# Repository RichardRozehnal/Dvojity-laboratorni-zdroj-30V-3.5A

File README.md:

# Dvojitý laboratorní zdroj 30V / 3.5A

Napájecí zdroj s nastavitelným výstupním napětím 0-30V a nastavitelným omezením výstupního proudu 0-3.5A. Omezení proudu je indikováno červenou LEDkou.
Jedná se o dvoukanálový laboratorní zdroj.  Maximální proud, který jsem dostal z kanálu 1 je 3.5A a z kanálu 2 3.7A (po zkratování výstupních svorek).<br>
Použitý transformátor má několik sekundárních vinutí. Z nich jsem využil dvě hlavní, každé s výstupem 25V/4A a dvě pomocná s výstupem 12V/2A pro napájení panelových měřidel a ventilátorů.<br>
Zapnutí ventilátorů jsem nastavil na teplotu tranzistorů 60C, vypíná se při 46C.<br>
Čelní panel jsem nakreslil v Inkscape, vytiskl a potom přežehlil laminovací folií pro lepší vzhled, zpevnění a také ochranu tisku.<br>
Pro regulaci výstupního napětí a omezení proudu jsou použity 5-ti otáčkové potenciometry.<br>
Rozměr zdroje je 24cm x 15cm x 25cm, větrací otvory mají průměr 7mm a rozteč 10.4mm.

## Měření tvrdosti zdroje

| **nastavené napětí / napětí po zatížení (kanál 1 / kanál 2)** | **0.45A**   | **0.89A**   | **1.82A**     | **3A**         | **3.5A**      |
| :-----------------------------------------------------------: | :---------: | :---------: | :-----------: | :------------: | :-----------: |
| 5V                                                            | 5V / 5V     | 5V / 5V     | 5V / 5V       | 5V / 5V        | 5V / 5V       |
| 10V                                                           | 10V / 10V   | 10V / 10V   | 10V / 10V     | 10V / 10V      | 10V / 10V     |
| 20V                                                           | 20V / 20V   | 20V / 20V   | 20V /20V      | 20V / 20V      | 20V / 20V     |
| 25V                                                           |             |             |               | 24.5 V / 24.2V | 23.6V / 23.6V |
| 30V                                                           | 30V / 29.8V | 29V / 28.8V | 26.8V / 26.7V |                |               |

## Měření teplot a proudů (při otevřeném šasi)

|                                                       | nastavený proud  | Kanál 1  | Kanál 2  |
| ----------------------------------------------------- | :--------------: | :------: | :------: |
| Teplota tranzistorů KD502 (bez zapnutého ventilátoru) | 1A               | 54C      | 58C      |
| Teplota tranzistorů KD502 (bez zapnutého ventilátoru) | 2A               | přes 70C | přes 80C |
| Teplota tranzistorů KD502 (se zapnutým ventilátorem)  | 2A               | 55C      | 63C      |
| Teplota tranzistorů KD502 (se zapnutým ventilátorem)  | 3A               | 65C      | 76C      |
| Teplota tranzistorů KD502 (se zapnutým ventilátorem)  | max. 3.5A / 3.7A | 67C      | 84C      |
| Teplota rezistorů R7 a R8                             | 3A               | 80C      | 81C      |
| Teplota rezistorů R7 a R8                             | max. 3.5A / 3.7A | 92C      | 107C     |

## Seznam součástek

| **Ref**                          | **Qnty** | **Value**                               | **Cmp name** |
| -------------------------------- | :------: | --------------------------------------- | ------------ |
| 230V1,                           | 1        | 230V                                    | Conn\_01x02  |
| C1, C2,                          | 2        | 4700uF/63V/105C                         | CP           |
| C3, C4,                          | 2        | 47uF/50V                                | CP           |
| C5,                              | 1        | 220n CF1                                | C            |
| C6, C9,                          | 2        | 100pF                                   | C            |
| C7,                              | 1        | 10uF/50V                                | CP           |
| C8,                              | 1        | 330pF                                   | C            |
| C10, C14,                        | 2        | 100nF                                   | C            |
| C13,                             | 1        | 330nF                                   | C            |
| C15, C16,                        | 2        | 1000uF/25V                              | CP           |
| D1, D2, D3, D4,                  | 4        | P1000M                                  | D            |
| D5, D6,                          | 2        | 1N4148                                  | D            |
| D7,                              | 1        | 1N4734A (5V6)                           | D\_Zener     |
| D8,                              | 1        | BZX83V005.6                             | D\_Zener     |
| D9, D10,                         | 2        | 1N4148                                  | D            |
| D11, D14,                        | 2        | S1M                                     | D            |
| D12,                             | 1        | LED 5mm červená                         | LED          |
| D13,                             | 1        | KBP307                                  | KBP307       |
| D15,                             | 1        | LED 5mm žlutá                           | LED          |
| F1,                              | 1        | 6A                                      | Fuse         |
| F2,                              | 1        | 500mA                                   | Fuse         |
| F3,                              | 1        | 2A                                      | Fuse         |
| IO1, IO2, IO3,                   | 3        | TL071                                   | TL071        |
| J1,                              | 1        | výstup na svorky                        | Conn\_01x02  |
| J2,                              | 1        | výstup na externí tranzistory           | Conn\_01x03  |
| J3,                              | 1        | napájení panelového měřidla             | Conn\_01x02  |
| M1,                              | 1        | ventilátor                              | Fan          |
| P1, P2,                          | 2        | 10K (5ot.)                              | R\_Variable  |
| R1,                              | 1        | 2K2/2W                                  | R            |
| R2,                              | 1        | 220R                                    | R            |
| R3,                              | 1        | 82R                                     | R            |
| R4, R29,                         | 2        | 4K7                                     | R            |
| R5, R6, R13, R20, R21, R28, R30, | 7        | 10K                                     | R            |
| R7, R8,                          | 2        | 1R0/10W                                 | R            |
| R9, R19,                         | 2        | 2K2                                     | R            |
| R10,                             | 1        | 270K                                    | R            |
| R11, R25,                        | 2        | 27K                                     | R            |
| R12, R18,                        | 2        | 56K                                     | R            |
| R14,                             | 1        | 1K5                                     | R            |
| R15, R16, R32,                   | 3        | 1K0                                     | R            |
| R17,                             | 1        | 33R                                     | R            |
| R22,                             | 1        | 1K8                                     | R            |
| R23, R24,                        | 2        | 0R33/5W                                 | R            |
| R26,                             | 1        | 100K                                    | RTRIM        |
| R27,                             | 1        | 10K                                     | RTRIM        |
| R31,                             | 1        | 1M5                                     | R            |
| R33,                             | 1        | 1K8                                     | R            |
| SW1,                             | 1        | Hlavní vypínač                          | SW\_DPST     |
| SW2,                             | 1        | Vypínač                                 | SW\_DPST\_2  |
| T1, T2, T6,                      | 3        | MMBT2222                                | Q\_NPN\_BEC  |
| T3,                              | 1        | BC857                                   | Q\_PNP\_BEC  |
| T4, T5,                          | 2        | KD502                                   | Q\_NPN\_BEC  |
| TH1,                             | 1        | KTY81-210                               | KTY81        |
| TR1,                             | 1        | Trafo                                   | Trafo        |
| U2,                              | 1        | L7812                                   | L7812        |
| U3,                              | 1        | LM358                                   | LM358        |
|                                  |          |                                         |              |
|                                  | 2        | hmatník na potenciometry                |              |
|                                  | 2        | konektor, banánky                       |              |
|                                  | 2        | mřižka na ventilátor                    |              |
|                                  | 1        | chladič S25AN (15C/W) na TO-220 (L7812) |              |
|                                  | 1        | panelové měřidlo                        |              |
|                                  | 1        | chladič pro KD502                       |              |

## Další obrázky

Původní zapojení, ze kterého jsem vycházel, je [tady](http://bcmp.cz/laboratorni-zdroj-0-30v-2ma-4a/).

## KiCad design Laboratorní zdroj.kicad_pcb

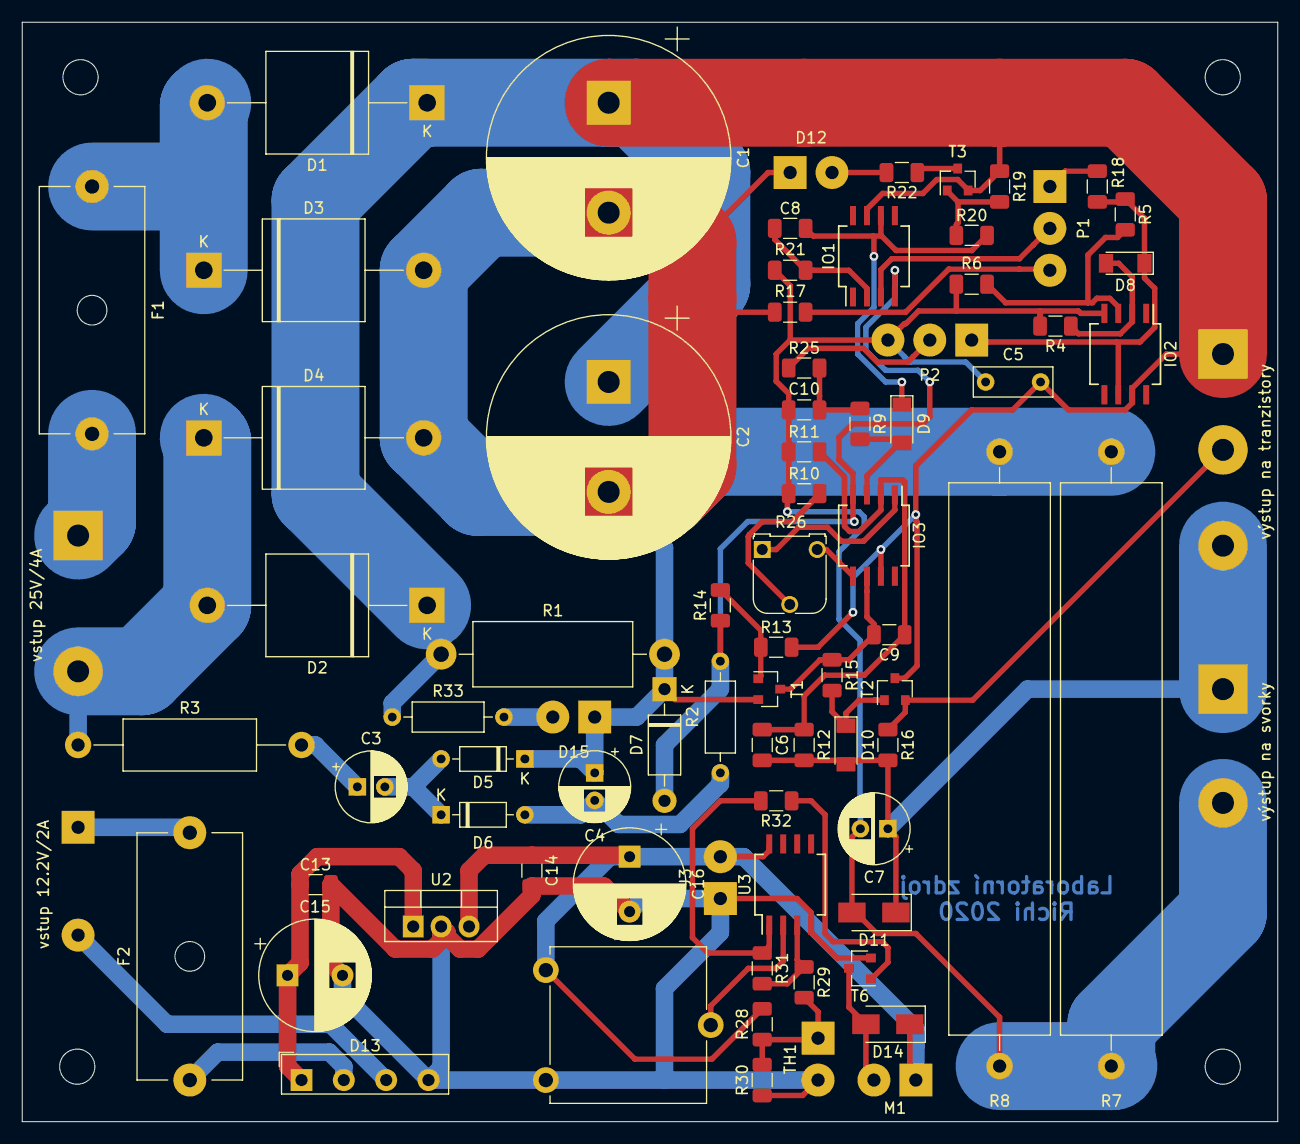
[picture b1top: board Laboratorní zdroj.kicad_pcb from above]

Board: 2 copper layers, 114.2 x 100.0 mm, 79 parts (0 on the bottom side), 44 nets.

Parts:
C1, C2: 4700uF/63V/105C; CP_Radial_D22.0mm_P10.00mm_SnapIn
C3, C4: 47uF/50V; CP_Radial_D6.3mm_P2.50mm
C5: 220n CF1; C_Rect_L7.0mm_W2.5mm_P5.00mm
C6, C9: 100pF; C_1206_3216Metric
C7: 10uF/50V; CP_Radial_D6.3mm_P2.50mm
C8: 330pF; C_1206_3216Metric
C10, C14: 100nF; C_1206_3216Metric
C13: 330nF; C_1206_3216Metric
C15, C16: 1000uF/25V; CP_Radial_D10.0mm_P5.00mm
D1, D2, D3, D4: P1000M; D_P600_R-6_P20.00mm_Horizontal
D5, D6: 1N4148; D_DO-35_SOD27_P7.62mm_Horizontal
D7: 1N4734A (5V6); D_DO-41_SOD81_P10.16mm_Horizontal
D8: BZX83V005.6; D_MiniMELF
D9, D10: 1N4148; D_MiniMELF
D11, D14: S1M; D_SMA
D12: LED 5mm červená; SolderWirePad_1x02_P3.81mm_Drill1.2mm
D13: KBP307; Diode_Bridge_KBP307_15.0x3.5x10.0mm_P4.0mm
D15: LED 5mm žlutá; SolderWirePad_1x02_P3.81mm_Drill1.2mm
F1: 6A; Fuseholder_Cylinder-5x20mm_Schurter_0031_8201_Horizontal_Op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
F2: 500mA; Fuseholder_Cylinder-5x20mm_Schurter_0031_8201_Horizontal_Op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
IO1, IO2, IO3: TL071; SO-8_5.3x6.2mm_P1.27mm
J3: napájení panelového měřidla; SolderWirePad_1x02_P3.81mm_Drill1.2mm
M1: ventilátor; SolderWirePad_1x02_P3.81mm_Drill1.2mm
P1, P2: 10K (5ot.); SolderWirePad_1x03_P3.81mm_Drill1.2mm
R1: 2K2/2W; R_Axial_DIN0614_L14.3mm_D5.7mm_P20.32mm_Horizontal
R2: 220R; R_Axial_DIN0207_L6.3mm_D2.5mm_P10.16mm_Horizontal
R3: 82R; R_Axial_DIN0414_L11.9mm_D4.5mm_P20.32mm_Horizontal
R4, R29: 4K7; R_1206_3216Metric
R5, R6, R13, R20, R21, R28, R30: 10K; R_1206_3216Metric
R7, R8: 1R0/10W; R_Axial_Power_L50.0mm_W9.0mm_P55.88mm
R9, R19: 2K2; R_1206_3216Metric
R10: 270K; R_1206_3216Metric
R11, R25: 27K; R_1206_3216Metric
R12, R18: 56K; R_1206_3216Metric
R14: 1K5; R_1206_3216Metric
R15, R16, R32: 1K0; R_1206_3216Metric
R17: 33R; R_1206_3216Metric
R22: 1K8; R_1206_3216Metric
R26: 100K; Potentiometer_Runtron_RM-065_Vertical
R27: 10K; Potentiometer_ACP_CA14V-15_Vertical
R31: 1M5; R_1206_3216Metric
R33: 1K8; R_Axial_DIN0207_L6.3mm_D2.5mm_P10.16mm_Horizontal
T1, T2, T6: MMBT2222; SOT-23
T3: BC857; SOT-23
TH1: KTY81-210; SolderWirePad_1x02_P3.81mm_Drill1.2mm
U2: L7812; TO-220-3_Vertical
U3: LM358; SO-8_5.3x6.2mm_P1.27mm
vstup 25V/4A: Trafo
výstup na svorky: výstup na svorky; SolderWirePad_1x02_P10.414mm_Drill2mm
výstup na tranzistory: výstup na externí tranzistory; SolderWirePad_1x03_P5.715mm_Drill2mm

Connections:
unnamed: C1.1, C2.1, C5.2, D1.1, D2.1, IO1.7, IO2.7, IO3.7, R1.1, R13.2, R19.1, R33.1, T2.3, T3.2, výstup na tranzistory.1
unnamed: C1.2, C2.2, C4.1, D3.2, D4.2, D5.1, D7.1, D12.1, D15.1, R1.2, R7.1, R8.1, R17.2, T1.2
unnamed: C3.1, R3.2
unnamed: C3.2, D5.2, D6.1
unnamed: C4.2, D6.2, R2.2
unnamed: C6.1, C9.1, IO3.2, R11.2, R12.1
unnamed: C6.2, C7.1, D10.2, D11.1, R12.2, R16.2, výstup na svorky.1, výstup na tranzistory.3
unnamed: C8.1, IO1.2, R21.1
unnamed: C8.2, D9.1, IO1.6, R20.2
unnamed: C9.2, IO3.6, R15.1, T1.3
unnamed: C10.1, R9.1, R25.2
unnamed: C5.1, C7.2, C10.2, D11.2, IO2.4, P2.3, R4.2, R6.2, R7.2, R8.2, R10.1, R11.1, R21.2, výstup na svorky.2
unnamed: C13.1, C15.1, D13.1, U2.1
unnamed: C13.2, C14.2, C15.2, C16.2, D13.4, J3.1, R27.1, R30.1, T6.2, TH1.2, U2.2, U3.4
unnamed: C14.1, C16.1, D14.1, J3.2, M1.1, R27.3, R28.2, U2.3, U3.8
unnamed: D1.2, D3.1, F1.1
unnamed: D2.2, D4.1, R3.1, vstup 25V/4A.4
unnamed: D7.2, IO1.4, IO3.4, R2.1, R14.1
unnamed: D8.1, IO2.6, P2.1, R5.1, R18.1
unnamed: D8.2, IO2.2, R4.1
unnamed: D9.2, IO3.3, R9.2
unnamed: D10.1, R15.2, T2.1
unnamed: D12.2, R22.2
unnamed: D13.2, F2.1
unnamed: D13.3, vstup 25V/4A.8
unnamed: D14.2, M1.2, T6.3
unnamed: D15.2, R33.2
unnamed: IO1.3, P1.2
unnamed: IO2.3, R5.2, R6.1
unnamed: IO3.1, R26.1
unnamed: IO3.5, R26.3
unnamed: R16.1, T2.2, výstup na tranzistory.2
unnamed: P1.1, R18.2
unnamed: P1.3, R17.1
unnamed: P2.2, R25.1
unnamed: R10.2, R26.2
unnamed: R13.1, R14.2, T1.1
unnamed: R19.2, R20.1, T3.1
unnamed: R22.1, T3.3
unnamed: R27.2, U3.2
unnamed: R28.1, R29.2, R30.2, TH1.1
unnamed: R29.1, R31.2, U3.3
unnamed: R31.1, R32.2, U3.1
unnamed: R32.1, T6.1

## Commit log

2020-12-02 Create LICENSE
